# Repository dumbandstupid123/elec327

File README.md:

ELEC327
=======
- labs 1 through 6 completed

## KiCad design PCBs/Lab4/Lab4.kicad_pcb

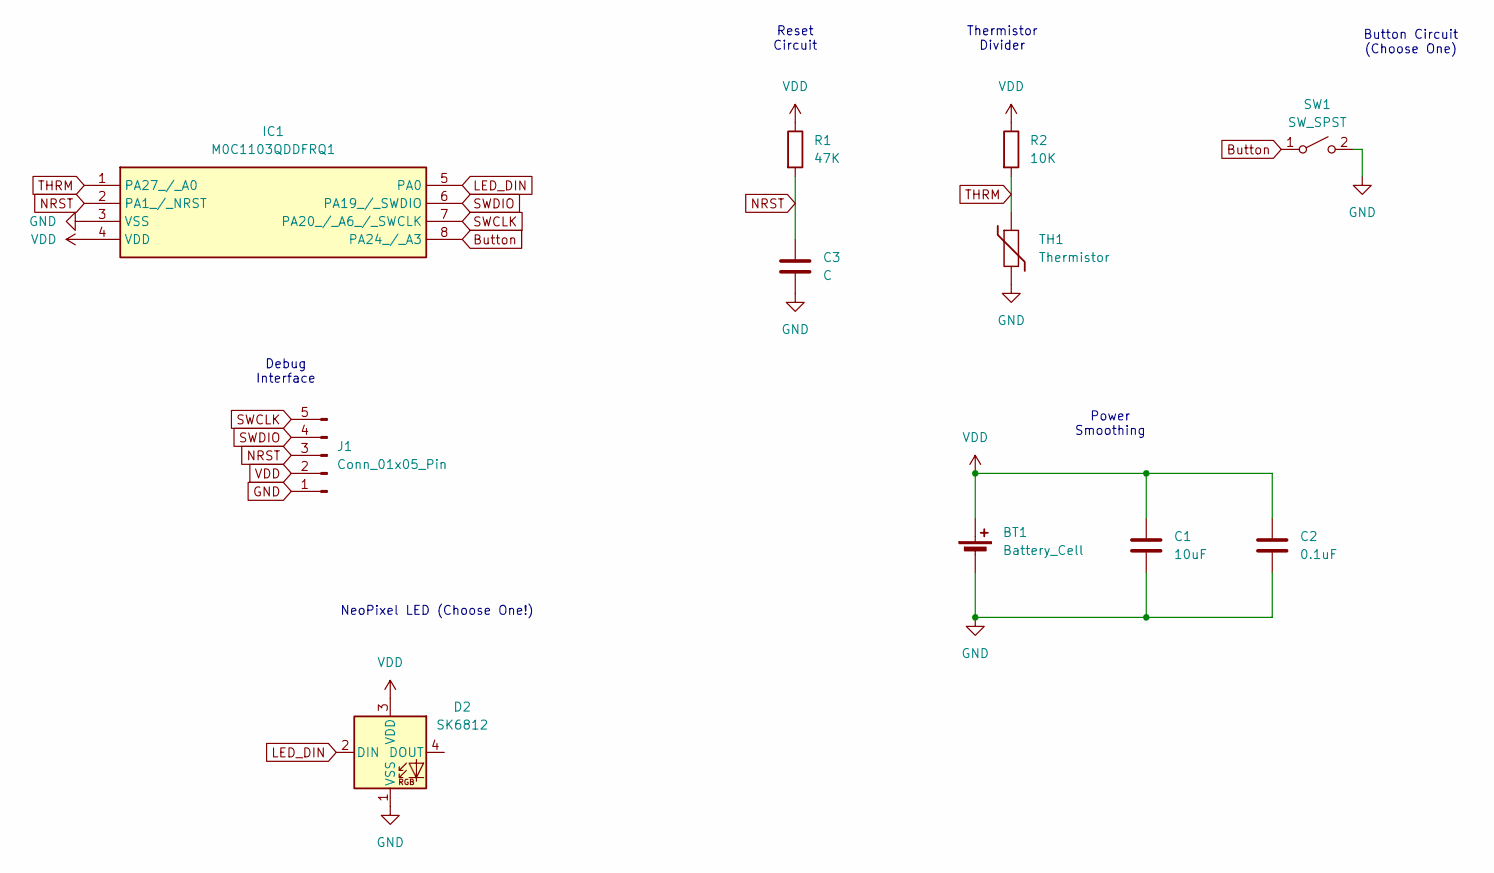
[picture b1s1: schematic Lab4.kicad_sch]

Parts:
BT1: Battery_Cell; BatteryHolder_Keystone_3001_1x12mm
C1: 10uF; C_1206_3216Metric_Pad1.33x1.80mm_HandSolder
C2: 0.1uF; C_1206_3216Metric_Pad1.33x1.80mm_HandSolder
C3: C; C_1206_3216Metric_Pad1.33x1.80mm_HandSolder
D2: SK6812; LED_SK6812_PLCC4_5.0x5.0mm_P3.2mm
IC1: M0C1103QDDFRQ1; SOT-23-8; Mouser Part Number 595-M0C1103QDDFRQ1
J1: Conn_01x05_Pin; PinHeader_1x05_P2.54mm_Vertical
R1: 47K; R_1206_3216Metric_Pad1.30x1.75mm_HandSolder
R2: 10K; R_1206_3216Metric_Pad1.30x1.75mm_HandSolder
SW1: SW_SPST; SW_PUSH_6mm_H5mm
TH1: Thermistor; R_1206_3216Metric_Pad1.30x1.75mm_HandSolder

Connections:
Button: IC1.8 (PA24_/_A3), SW1.1 (A); also elsewhere on the board
GND: BT1.2 (-), C1.2, C2.2, C3.2, D2.1 (VSS), IC1.3 (VSS), J1.1, SW1.2 (B), TH1.2; also elsewhere on the board
LED_DIN: D2.2 (DIN), IC1.5 (PA0)
NRST: C3.1, IC1.2 (PA1_/_NRST), J1.3, R1.2
SWCLK: IC1.7 (PA20_/_A6_/_SWCLK), J1.5
SWDIO: IC1.6 (PA19_/_SWDIO), J1.4
THRM: IC1.1 (PA27_/_A0), R2.2, TH1.1
VDD: BT1.1 (+), C1.1, C2.1, D2.3 (VDD), IC1.4 (VDD), J1.2, R1.1, R2.1

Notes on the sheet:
Reset Circuit
NeoPixel LED (Choose One!)
Power Smoothing
Debug Interface
Thermistor Divider
Button Circuit (Choose One)

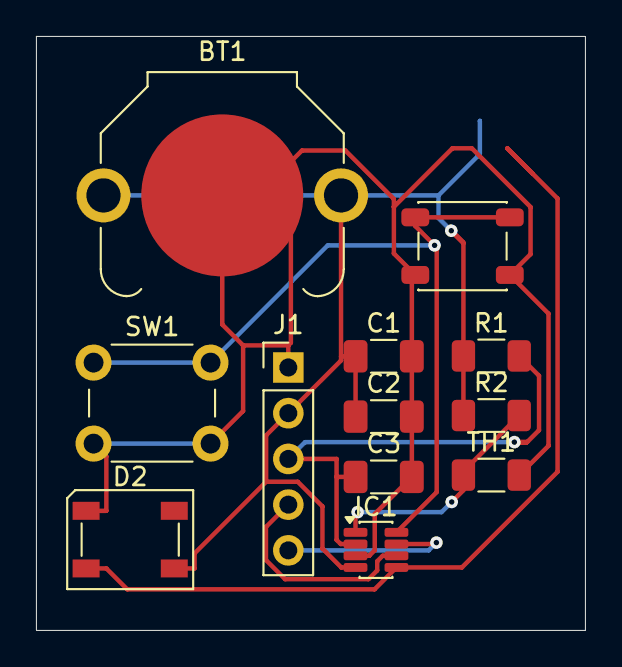
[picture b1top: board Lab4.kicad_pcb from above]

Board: 2 copper layers, 30.5 x 33.0 mm, 12 parts (0 on the bottom side), 8 nets.

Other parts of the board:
SW2: SW_SPST; SW_SPST_PTS647_Sx50

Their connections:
Button: SW2.1 (A); also elsewhere on the board
GND: SW2.2 (B); also elsewhere on the board

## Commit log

2026-03-04 Complete Labs 1-6: firmware and PCB submissions
    Labs 1-3: GPIO/state machine LED control with button input
    Lab 4: KiCad Simon PCB design
    Lab 5: PWM buzzer + Mary Had a Little Lamb state machine
    Lab 6: SPI RGB LED control synchronized to song and button presses
2026-03-04 Update Lab6 startup file
